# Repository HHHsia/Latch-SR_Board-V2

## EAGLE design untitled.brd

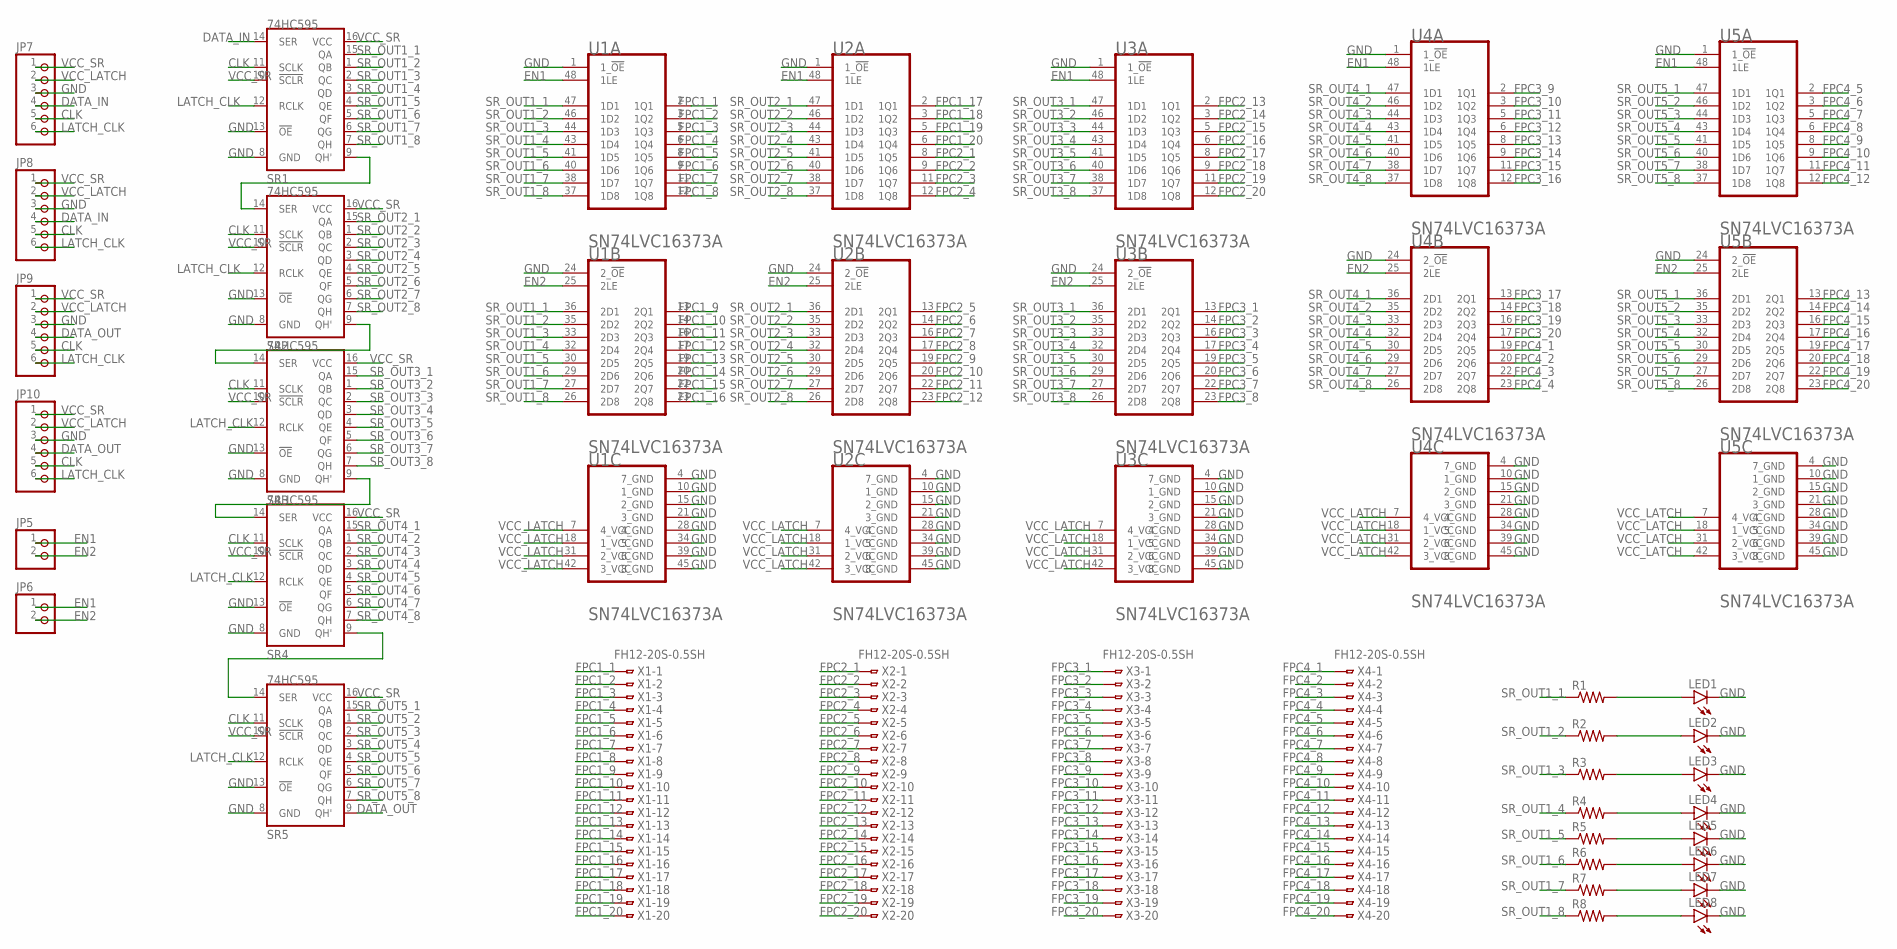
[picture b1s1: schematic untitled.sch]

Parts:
JP5, JP6: PINHD-1X2; 1X02
JP7, JP8, JP9, JP10: PINHD-1X6; 1X06
LED1, LED2, LED3, LED4, LED5, LED6, LED7, LED8: LEDCHIP-LED0805; CHIP-LED0805
R1, R2, R3, R4, R5, R6, R7, R8: R-US_R0805; R0805
SR1, SR2, SR3, SR4, SR5: 74HC595; SO16
U1, U2, U3, U4, U5: TEXAS_INSTRUMENTS_SN74LVC16373ATEXAS_INSTRUMENTS_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; TEXAS_INSTRUMENTS_SN74LVC16373A_2
X1, X2, X3, X4: FH12-20S-0.5SH

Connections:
CLK: JP7.5, JP8.5, JP9.5, JP10.5, SR1.11 (SCLK), SR2.11 (SCLK), SR3.11 (SCLK), SR4.11 (SCLK), SR5.11 (SCLK)
DATA_IN: JP7.4, JP8.4, SR1.14 (SER)
DATA_OUT: JP9.4, JP10.4, SR5.9 (QH')
EN1: JP5.1, JP6.1, U1.48 (1LE), U2.48 (1LE), U3.48 (1LE), U4.48 (1LE), U5.48 (1LE)
EN2: JP5.2, JP6.2, U1.25 (2LE), U2.25 (2LE), U3.25 (2LE), U4.25 (2LE), U5.25 (2LE)
FPC1_1: U1.2 (1Q1), X1.1
FPC1_2: U1.3 (1Q2), X1.2
FPC1_3: U1.5 (1Q3), X1.3
FPC1_4: U1.6 (1Q4), X1.4
FPC1_5: U1.8 (1Q5), X1.5
FPC1_6: U1.9 (1Q6), X1.6
FPC1_7: U1.11 (1Q7), X1.7
FPC1_8: U1.12 (1Q8), X1.8
FPC1_9: U1.13 (2Q1), X1.9
FPC1_10: U1.14 (2Q2), X1.10
FPC1_11: U1.16 (2Q3), X1.11
FPC1_12: U1.17 (2Q4), X1.12
FPC1_13: U1.19 (2Q5), X1.13
FPC1_14: U1.20 (2Q6), X1.14
FPC1_15: U1.22 (2Q7), X1.15
FPC1_16: U1.23 (2Q8), X1.16
FPC1_17: U2.2 (1Q1), X1.17
FPC1_18: U2.3 (1Q2), X1.18
FPC1_19: U2.5 (1Q3), X1.19
FPC1_20: U2.6 (1Q4), X1.20
FPC2_1: U2.8 (1Q5), X2.1
FPC2_2: U2.9 (1Q6), X2.2
FPC2_3: U2.11 (1Q7), X2.3
FPC2_4: U2.12 (1Q8), X2.4
FPC2_5: U2.13 (2Q1), X2.5
FPC2_6: U2.14 (2Q2), X2.6
FPC2_7: U2.16 (2Q3), X2.7
FPC2_8: U2.17 (2Q4), X2.8
FPC2_9: U2.19 (2Q5), X2.9
FPC2_10: U2.20 (2Q6), X2.10
FPC2_11: U2.22 (2Q7), X2.11
FPC2_12: U2.23 (2Q8), X2.12
FPC2_13: U3.2 (1Q1), X2.13
FPC2_14: U3.3 (1Q2), X2.14
FPC2_15: U3.5 (1Q3), X2.15
FPC2_16: U3.6 (1Q4), X2.16
FPC2_17: U3.8 (1Q5), X2.17
FPC2_18: U3.9 (1Q6), X2.18
FPC2_19: U3.11 (1Q7), X2.19
FPC2_20: U3.12 (1Q8), X2.20
FPC3_1: U3.13 (2Q1), X3.1
FPC3_2: U3.14 (2Q2), X3.2
FPC3_3: U3.16 (2Q3), X3.3
FPC3_4: U3.17 (2Q4), X3.4
FPC3_5: U3.19 (2Q5), X3.5
FPC3_6: U3.20 (2Q6), X3.6
FPC3_7: U3.22 (2Q7), X3.7
FPC3_8: U3.23 (2Q8), X3.8
FPC3_9: U4.2 (1Q1), X3.9
FPC3_10: U4.3 (1Q2), X3.10
FPC3_11: U4.5 (1Q3), X3.11
FPC3_12: U4.6 (1Q4), X3.12
FPC3_13: U4.8 (1Q5), X3.13
FPC3_14: U4.9 (1Q6), X3.14
FPC3_15: U4.11 (1Q7), X3.15
FPC3_16: U4.12 (1Q8), X3.16
FPC3_17: U4.13 (2Q1), X3.17
FPC3_18: U4.14 (2Q2), X3.18
FPC3_19: U4.16 (2Q3), X3.19
FPC3_20: U4.17 (2Q4), X3.20
FPC4_1: U4.19 (2Q5), X4.1
FPC4_2: U4.20 (2Q6), X4.2
FPC4_3: U4.22 (2Q7), X4.3
FPC4_4: U4.23 (2Q8), X4.4
FPC4_5: U5.2 (1Q1), X4.5
FPC4_6: U5.3 (1Q2), X4.6
FPC4_7: U5.5 (1Q3), X4.7
FPC4_8: U5.6 (1Q4), X4.8
FPC4_9: U5.8 (1Q5), X4.9
FPC4_10: U5.9 (1Q6), X4.10
FPC4_11: U5.11 (1Q7), X4.11
FPC4_12: U5.12 (1Q8), X4.12
FPC4_13: U5.13 (2Q1), X4.13
FPC4_14: U5.14 (2Q2), X4.14
FPC4_15: U5.16 (2Q3), X4.15
FPC4_16: U5.17 (2Q4), X4.16
FPC4_17: U5.19 (2Q5), X4.17
FPC4_18: U5.20 (2Q6), X4.18
FPC4_19: U5.22 (2Q7), X4.19
FPC4_20: U5.23 (2Q8), X4.20
GND: JP7.3, JP8.3, JP9.3, JP10.3, LED1.C, LED2.C, LED3.C, LED4.C, LED5.C, LED6.C, LED7.C, LED8.C, SR1.8 (GND), SR1.13 (!OE), SR2.8 (GND), SR2.13 (!OE), SR3.8 (GND), SR3.13 (!OE), SR4.8 (GND), SR4.13 (!OE), SR5.8 (GND), SR5.13 (!OE), U1.1 (1_!OE!), U1.4 (7_GND), U1.10 (1_GND), U1.15 (2_GND), U1.21 (3_GND), U1.24 (2_!OE!), U1.28 (4_GND), U1.34 (5_GND), U1.39 (6_GND), U1.45 (8_GND), U2.1 (1_!OE!), U2.4 (7_GND), U2.10 (1_GND), U2.15 (2_GND), U2.21 (3_GND), U2.24 (2_!OE!), U2.28 (4_GND), U2.34 (5_GND), U2.39 (6_GND), U2.45 (8_GND), U3.1 (1_!OE!), U3.4 (7_GND), U3.10 (1_GND), U3.15 (2_GND), U3.21 (3_GND), U3.24 (2_!OE!), U3.28 (4_GND), U3.34 (5_GND), U3.39 (6_GND), U3.45 (8_GND), U4.1 (1_!OE!), U4.4 (7_GND), U4.10 (1_GND), U4.15 (2_GND), U4.21 (3_GND), U4.24 (2_!OE!), U4.28 (4_GND), U4.34 (5_GND), U4.39 (6_GND), U4.45 (8_GND), U5.1 (1_!OE!), U5.4 (7_GND), U5.10 (1_GND), U5.15 (2_GND), U5.21 (3_GND), U5.24 (2_!OE!), U5.28 (4_GND), U5.34 (5_GND), U5.39 (6_GND), U5.45 (8_GND)
LATCH_CLK: JP7.6, JP8.6, JP9.6, JP10.6, SR1.12 (RCLK), SR2.12 (RCLK), SR3.12 (RCLK), SR4.12 (RCLK), SR5.12 (RCLK)
unnamed: SR1.9 (QH'), SR2.14 (SER)
unnamed: SR4.9 (QH'), SR5.14 (SER)
unnamed: LED1.A, R1.2
unnamed: LED2.A, R2.2
unnamed: LED3.A, R3.2
unnamed: LED4.A, R4.2
unnamed: LED5.A, R5.2
unnamed: SR2.9 (QH'), SR3.14 (SER)
unnamed: LED6.A, R6.2
unnamed: LED7.A, R7.2
unnamed: LED8.A, R8.2
unnamed: SR3.9 (QH'), SR4.14 (SER)
SR_OUT1_1: R1.1, SR1.15 (QA), U1.36 (2D1), U1.47 (1D1)
SR_OUT1_2: R2.1, SR1.1 (QB), U1.35 (2D2), U1.46 (1D2)
SR_OUT1_3: R3.1, SR1.2 (QC), U1.33 (2D3), U1.44 (1D3)
SR_OUT1_4: R4.1, SR1.3 (QD), U1.32 (2D4), U1.43 (1D4)
SR_OUT1_5: R5.1, SR1.4 (QE), U1.30 (2D5), U1.41 (1D5)
SR_OUT1_6: R6.1, SR1.5 (QF), U1.29 (2D6), U1.40 (1D6)
SR_OUT1_7: R7.1, SR1.6 (QG), U1.27 (2D7), U1.38 (1D7)
SR_OUT1_8: R8.1, SR1.7 (QH), U1.26 (2D8), U1.37 (1D8)
SR_OUT2_1: SR2.15 (QA), U2.36 (2D1), U2.47 (1D1)
SR_OUT2_2: SR2.1 (QB), U2.35 (2D2), U2.46 (1D2)
SR_OUT2_3: SR2.2 (QC), U2.33 (2D3), U2.44 (1D3)
SR_OUT2_4: SR2.3 (QD), U2.32 (2D4), U2.43 (1D4)
SR_OUT2_5: SR2.4 (QE), U2.30 (2D5), U2.41 (1D5)
SR_OUT2_6: SR2.5 (QF), U2.29 (2D6), U2.40 (1D6)
SR_OUT2_7: SR2.6 (QG), U2.27 (2D7), U2.38 (1D7)
SR_OUT2_8: SR2.7 (QH), U2.26 (2D8), U2.37 (1D8)
SR_OUT3_1: SR3.15 (QA), U3.36 (2D1), U3.47 (1D1)
SR_OUT3_2: SR3.1 (QB), U3.35 (2D2), U3.46 (1D2)
SR_OUT3_3: SR3.2 (QC), U3.33 (2D3), U3.44 (1D3)
SR_OUT3_4: SR3.3 (QD), U3.32 (2D4), U3.43 (1D4)
SR_OUT3_5: SR3.4 (QE), U3.30 (2D5), U3.41 (1D5)
SR_OUT3_6: SR3.5 (QF), U3.29 (2D6), U3.40 (1D6)
SR_OUT3_7: SR3.6 (QG), U3.27 (2D7), U3.38 (1D7)
SR_OUT3_8: SR3.7 (QH), U3.26 (2D8), U3.37 (1D8)
SR_OUT4_1: SR4.15 (QA), U4.36 (2D1), U4.47 (1D1)
SR_OUT4_2: SR4.1 (QB), U4.35 (2D2), U4.46 (1D2)
SR_OUT4_3: SR4.2 (QC), U4.33 (2D3), U4.44 (1D3)
SR_OUT4_4: SR4.3 (QD), U4.32 (2D4), U4.43 (1D4)
SR_OUT4_5: SR4.4 (QE), U4.30 (2D5), U4.41 (1D5)
SR_OUT4_6: SR4.5 (QF), U4.29 (2D6), U4.40 (1D6)
SR_OUT4_7: SR4.6 (QG), U4.27 (2D7), U4.38 (1D7)
SR_OUT4_8: SR4.7 (QH), U4.26 (2D8), U4.37 (1D8)
SR_OUT5_1: SR5.15 (QA), U5.36 (2D1), U5.47 (1D1)
SR_OUT5_2: SR5.1 (QB), U5.35 (2D2), U5.46 (1D2)
SR_OUT5_3: SR5.2 (QC), U5.33 (2D3), U5.44 (1D3)
SR_OUT5_4: SR5.3 (QD), U5.32 (2D4), U5.43 (1D4)
SR_OUT5_5: SR5.4 (QE), U5.30 (2D5), U5.41 (1D5)
SR_OUT5_6: SR5.5 (QF), U5.29 (2D6), U5.40 (1D6)
SR_OUT5_7: SR5.6 (QG), U5.27 (2D7), U5.38 (1D7)
SR_OUT5_8: SR5.7 (QH), U5.26 (2D8), U5.37 (1D8)
VCC_LATCH: JP7.2, JP8.2, JP9.2, JP10.2, U1.7 (4_VCC), U1.18 (1_VCC), U1.31 (2_VCC), U1.42 (3_VCC), U2.7 (4_VCC), U2.18 (1_VCC), U2.31 (2_VCC), U2.42 (3_VCC), U3.7 (4_VCC), U3.18 (1_VCC), U3.31 (2_VCC), U3.42 (3_VCC), U4.7 (4_VCC), U4.18 (1_VCC), U4.31 (2_VCC), U4.42 (3_VCC), U5.7 (4_VCC), U5.18 (1_VCC), U5.31 (2_VCC), U5.42 (3_VCC)
VCC_SR: JP7.1, JP8.1, JP9.1, JP10.1, SR1.10 (!SCLR), SR1.16 (VCC), SR2.10 (!SCLR), SR2.16 (VCC), SR3.10 (!SCLR), SR3.16 (VCC), SR4.10 (!SCLR), SR4.16 (VCC), SR5.10 (!SCLR), SR5.16 (VCC)

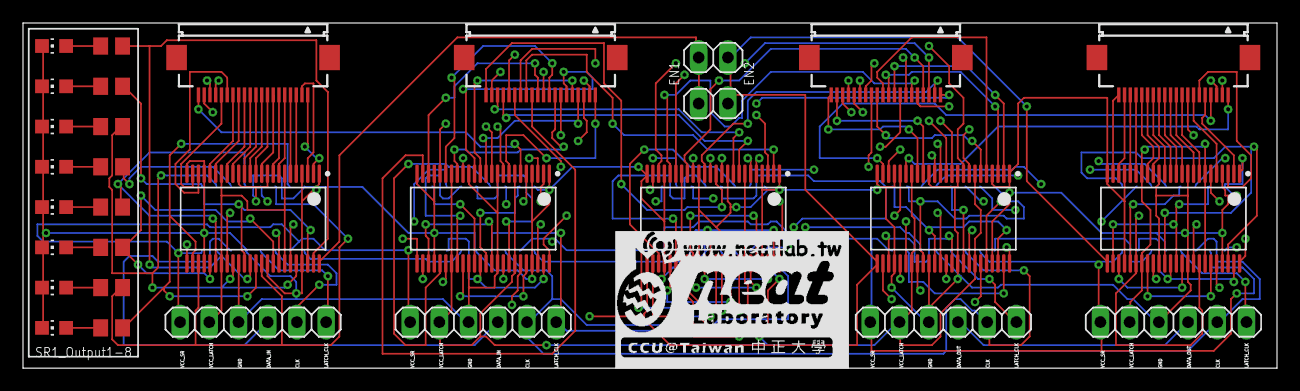
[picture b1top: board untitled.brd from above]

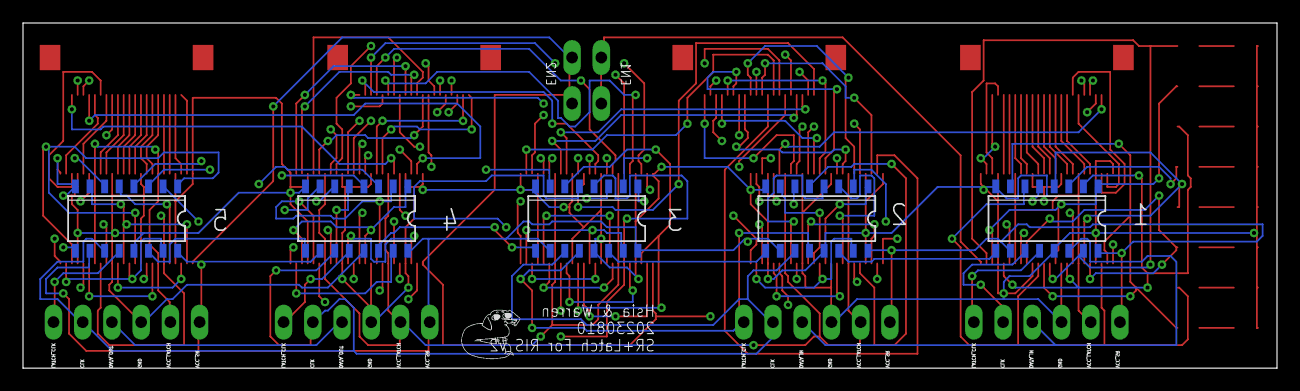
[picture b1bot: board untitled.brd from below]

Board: 4 copper layers, 109.0 x 30.0 mm, 37 parts (5 on the bottom side), 141 nets.

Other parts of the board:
U$1: LOGO_SCALE_2.0

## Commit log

2024-07-05 0705
